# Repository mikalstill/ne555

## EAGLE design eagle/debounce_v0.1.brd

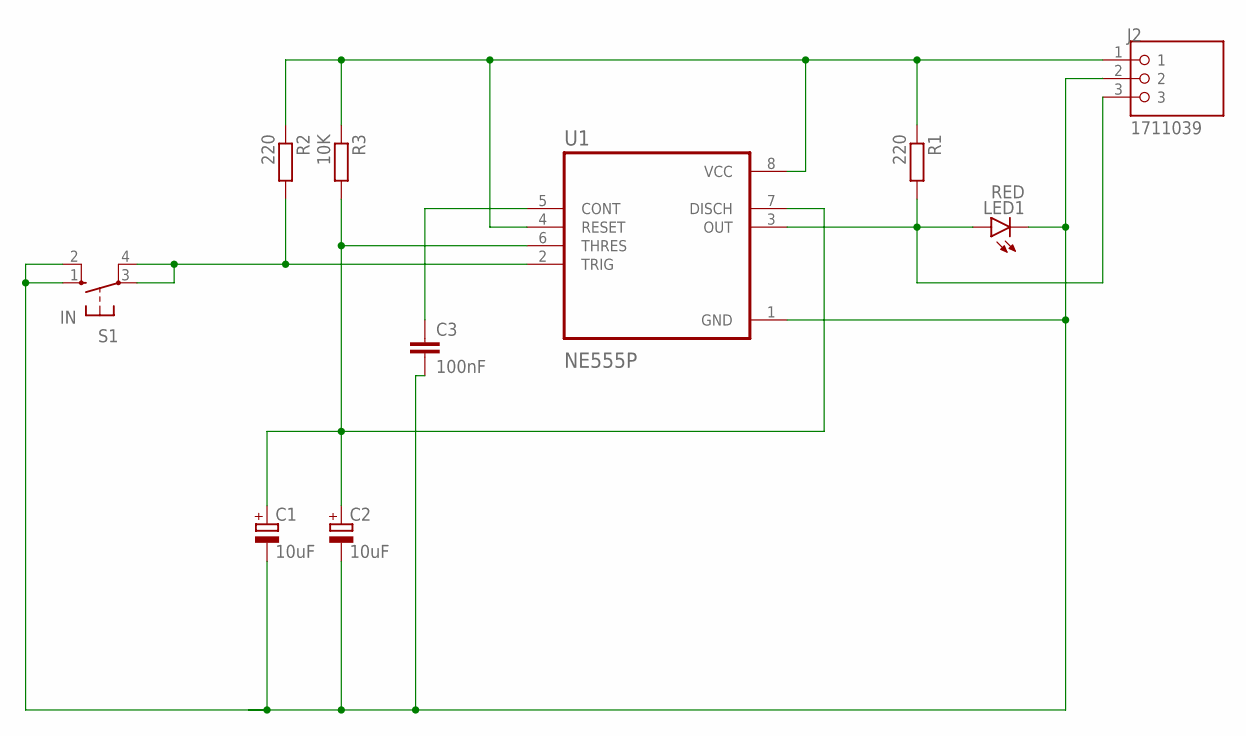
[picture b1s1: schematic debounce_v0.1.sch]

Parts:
C1, C2: 10uF; E2,5-6
C3: 100nF; RCL_C025-025X050
J2: 1711039; PHOENIX_1711039
LED1: RED; LED3MM
R1, R2: 220; RCL_0207/7
R3: 10K; RCL_0207/7
S1: IN; B3F-10XX
U1: NE555P; DIP794W45P254L959H508Q8

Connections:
CONT: C3.1, U1.5 (CONT)
DISCH/THRES: C1.+, C2.+, R3.2, U1.6 (THRES), U1.7 (DISCH)
GND: C1.-, C2.-, C3.2, J2.2, LED1.K (C), S1.1 (S), S1.2 (S1), U1.1 (GND)
OUT: J2.3, LED1.A, R1.2, U1.3 (OUT)
TRIG: R2.2, S1.3, S1.4 (P1), U1.2 (TRIG)
VCC: J2.1, R1.1, R2.1, R3.1, U1.4 (RESET), U1.8 (VCC)

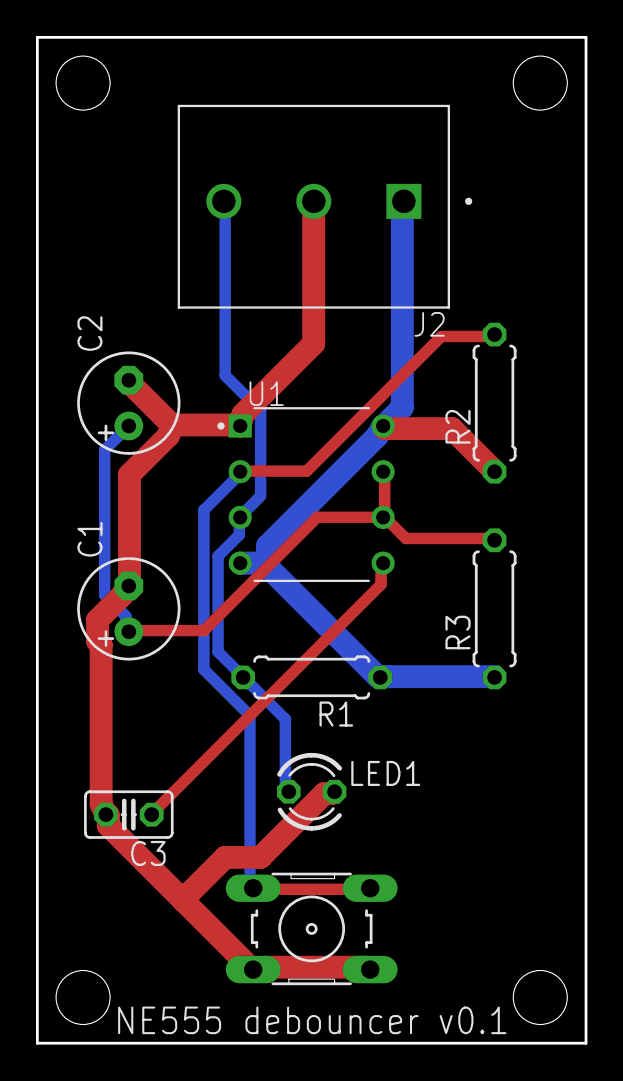
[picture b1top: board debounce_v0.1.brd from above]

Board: 2 copper layers, 30.5 x 55.9 mm, 10 parts (0 on the bottom side), 6 nets.

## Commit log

2024-07-28 Simple debouncer board.
